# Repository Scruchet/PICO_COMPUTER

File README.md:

# PICO Computer Project: Motherboard

Welcome to my PICO Computer project repository. This section consolidates all the source files written in the C language used by my motherboard, as well as the electronic components created with KiCad. The primary goal of this project is to create a motherboard that can be connected to other boards (screen, keyboard, network) to build a Pico Computer.

## Part 1: Motherboard
You can find all the plans for my board in the **Motherboard_pico** directory.

### Features
This board is composed of multiple components. The main IC is the Atmega328p, which acts as the processor. The FTDI serves as the connection between the USB port and the Atmega328p (it does not include USB). The AT45DB641E is the storage component of the computer. As this component works with 3.3V signals, a buffer is needed to convert the 5V signals from the Atmega328p to 3.3V. To connect all the other cards, there are 5 HE10 connectors. All the different cards communicate using SPI (MOSI, MISO, SS, SCK).

## Part 2: Source Section (src)

This section includes all the source files written in the C language used by my motherboard. In addition to the source files, there is also a test folder to demonstrate various evaluations performed during the project's development.

### Module Details

#### Makefile
The Makefile enables project compilation and management. Refer to this file for details on compilation, linking, and other build tasks. In each directory, you can run the code (excluding files without main.c) and upload the code using the `make upload` command.

#### Memory
The Memory directory contains files related to memory management, including handling a specific flash memory (AT45DB641E).

#### Scheduler
The Scheduler module includes files necessary for implementing a scheduler. Refer to `makefile`, `scheduler.c`, and `scheduler.h` for more details.

#### SPI
The SPI module contains the files `spi.c` and `spi.h` for managing communication via the Serial Peripheral Interface (SPI) bus.

#### UART
The UART module includes the files `UART.c` and `UART.h`, dedicated to asynchronous serial communication (UART).

#### Tests
The Tests directory includes several subdirectories, each containing specific tests.

- `7seg`: Tests related to the 7-segment display (https://www.sparkfun.com/products/11441).
- `Mat_leds`: Tests for the LED matrix (https://www.sparkfun.com/products/retired/760).
- `Mem`: Tests for memory management.
- `UART_SPI`: Tests for UART and SPI modules.

# Contact
Thank you for visiting my project. If you have any comments or questions, please feel free to contact me via email at the following address: cruchetsimon@gmail.com

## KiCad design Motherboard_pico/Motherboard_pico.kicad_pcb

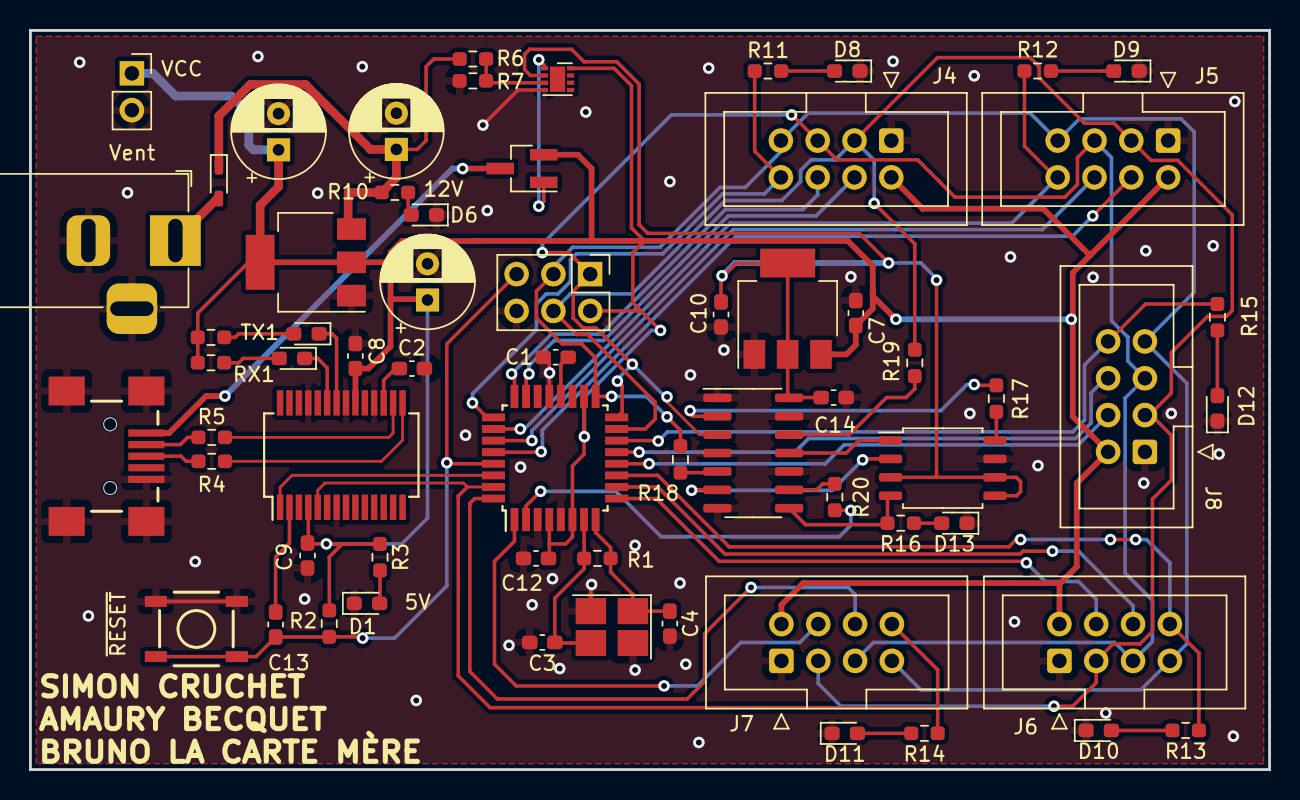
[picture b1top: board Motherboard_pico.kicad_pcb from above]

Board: 2 copper layers, 85.5 x 51.0 mm, 64 parts (0 on the bottom side), 58 nets.

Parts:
C1, C8, C9, C12, C13, C14: 100nF; C_0603_1608Metric_Pad1.08x0.95mm_HandSolder
C2: C; C_0603_1608Metric_Pad1.08x0.95mm_HandSolder
C3, C4: 22pF; C_0603_1608Metric_Pad1.08x0.95mm_HandSolder
C5: 4.7µF; CP_Radial_D6.3mm_P2.50mm
C6, C11: 47µF; CP_Radial_D6.3mm_P2.50mm
C7, C10: 1µF; C_0603_1608Metric_Pad1.08x0.95mm_HandSolder
D1, D6, D8, D9, D10, D11, D12, D13: LED; LED_0603_1608Metric_Pad1.05x0.95mm_HandSolder
D7: D; D_SC-80_HandSoldering
IC1: AT45DB641E-SHN2B-T; SOIC-8_5.275x5.275mm_P1.27mm
J1: Barrel_Jack_Switch_Pin3Ring; BarrelJack_Horizontal
J2: AVR-ISP-6; PinHeader_2x03_P2.54mm_Vertical
J3: Conn_01x02_Socket; PinSocket_1x02_P2.54mm_Vertical
J4, J5, J6, J7, J8: Conn_02x04_Counter_Clockwise; IDC-Header_2x04_P2.54mm_Vertical
J9: USB_MINI-B_SMT; USB-MINIB
Q1: FDN340P; SOT-23_Handsoldering
R1: 1MΩ; R_0603_1608Metric_Pad0.98x0.95mm_HandSolder
R2: 10KΩ; R_0603_1608Metric_Pad0.98x0.95mm_HandSolder
R3, R8, R9: 500Ω; R_0603_1608Metric_Pad0.98x0.95mm_HandSolder
R4, R5: 22Ω; R_0603_1608Metric_Pad0.98x0.95mm_HandSolder
R6, R7: 10k; R_0603_1608Metric_Pad0.98x0.95mm_HandSolder
R10: 1kΩ; R_0603_1608Metric_Pad0.98x0.95mm_HandSolder
R11, R12, R13, R14, R15, R16: 1k; R_0603_1608Metric_Pad0.98x0.95mm_HandSolder
R17, R18, R19, R20: 3.3k; R_0603_1608Metric_Pad0.98x0.95mm_HandSolder
RX1: LED; LED_0603_1608Metric_Pad1.05x0.95mm_HandSolder
S1: MOMENTARY-SWITCH-SPST-2-SMD-5.2MM; TACTILE_SWITCH_SMD_5.2MM
TX1: LED; LED_0603_1608Metric_Pad1.05x0.95mm_HandSolder
U1: ATmega328P-A; TQFP-32_7x7mm_P0.8mm
U2: LM358; DFN-8-1EP_2x2mm_P0.5mm_EP1.05x1.75mm
U3: AMS1117-5.0; SOT-223-3_TabPin2
U4: AMS1117; SOT-223-3_TabPin2
U5: 74LVC125; SOIC-14_3.9x8.7mm_P1.27mm
U6: FT232RL; SSOP-28_5.3x10.2mm_P0.65mm
Y1: 16MHz; Crystal_SMD_SeikoEpson_FA238-4Pin_3.2x2.5mm_HandSoldering

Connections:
3.3V: C10.1, C14.1, IC1.3 (~RESET), IC1.5 (~WP), IC1.6 (VCC), U2.2 (-), U4.2 (VO), U5.14 (VCC)
12V: C11.1, D7.1 (K), R6.2, R10.1, U3.3 (VI)
CBUS0: RX1.1 (K), U6.23 (CBUS0)
CBUS1: TX1.1 (K), U6.22 (CBUS1)
CS1: R20.1, U1.2 (PD4)
CS1_1: IC1.4 (~CS), R16.2, U5.8
CS2: J4.8, R11.2, U1.25 (PC2)
CS3: J5.8, R12.2, U1.26 (PC3)
CS4: J6.8, R13.2, U1.11 (PD7)
CS5: J7.8, R14.2, U1.31 (PD1), U6.5 (RXD)
CS6: J8.8, R15.2, U1.14 (PB2)
D+: R4.2, U6.15 (USBD+)
D-: R5.2, U6.16 (USBD-)
GND: C1.2, C2.2, C3.2, C4.2, C5.2, C6.2, C7.2, C8.2, C9.2, C10.2, C11.2, C12.2, C14.2, D1.1 (K), D6.1 (K), D8.1 (K), D9.1 (K), D10.1 (K), D11.1 (K), D12.1 (K), D13.1 (K), IC1.7 (GND), J1.2, J1.3, J2.6 (GND), J3.2, J4.1, J5.1, J6.1, J7.1, J8.1, J9.GND, J9.S1 (SHIELD), J9.S2 (SHIELD), J9.S3 (SHIELD), J9.S4 (SHIELD), R7.2, S1.1, S1.2, U1.3 (GND), U1.5 (GND), U1.21 (GND), U2.4 (V-), U3.1 (GND), U4.1 (ADJ), U5.1, U5.4, U5.7 (GND), U5.10, U5.13, U6.7 (GND), U6.18 (GND), U6.21 (GND), U6.25 (AGND), Y1.2, Y1.4
INT1: J4.4, U1.23 (PC0)
INT2: J5.4, U1.28 (PC5)
INT3: J6.4, U1.9 (PD5)
INT4: J7.4, U1.1 (PD3)
INT5: J8.4, U1.12 (PB0)
MISO: J2.1 (MISO), J4.5, J5.5, J6.5, J7.5, J8.5, U1.16 (PB4), U5.3
MISO_1: IC1.8 (SO), R17.1
MOSI: J2.4 (MOSI), J4.3, J5.3, J6.3, J7.3, J8.3, R19.1, U1.15 (PB3)
MOSI_1: IC1.1 (SI), U5.11
unnamed: D1.2 (A), R3.2
unnamed: D6.2 (A), R10.2
unnamed: D7.2 (A), J1.1
unnamed: D8.2 (A), R11.1
unnamed: D9.2 (A), R12.1
unnamed: D10.2 (A), R13.1
unnamed: D11.2 (A), R14.1
unnamed: D12.2 (A), R15.1
unnamed: D13.2 (A), R16.1
unnamed: J9.D+, R4.1
unnamed: J9.D-, R5.1
unnamed: Q1.1 (G), U2.1
unnamed: R17.2, U5.2
unnamed: R18.2, U5.5
unnamed: R19.2, U5.12
unnamed: R20.2, U5.9
unnamed: R8.2, RX1.2 (A)
unnamed: R9.2, TX1.2 (A)
unnamed: C1.1, U1.20 (AREF)
unnamed: C3.1, R1.2, U1.7 (XTAL1/PB6), Y1.3
unnamed: C4.1, R1.1, U1.8 (XTAL2/PB7), Y1.1
unnamed: R6.1, R7.1, U2.3 (+)
unnamed: C2.1, U6.17 (3V3OUT)
unnamed: C13.2, U6.2 (DTR)
RESET: C13.1, J2.5 (~RST), R2.2, S1.3, S1.4, U1.29 (~RESET/PC6)
RST1: J4.6, U1.24 (PC1)
RST2: J5.6, U1.27 (PC4)
RST3: J6.6, U1.10 (PD6)
RST4: J7.6, U1.32 (PD2)
RST5: J8.6, U1.13 (PB1)
SCK: J2.3 (SCK), J4.7, J5.7, J6.7, J7.7, J8.7, R18.1, U1.17 (PB5)
SCK_1: IC1.2 (SCK), U5.6
TX: U1.30 (PD0), U6.1 (TXD)
VCC: C5.1, C6.1, C7.1, C8.1, C9.1, C12.1, J2.2 (VCC), J3.1, J4.2, J5.2, J6.2, J7.2, J8.2, Q1.2 (S), R2.1, R3.1, R8.1, R9.1, U1.4 (VCC), U1.6 (VCC), U1.18 (AVCC), U2.8 (V+), U3.2 (VO), U4.3 (VI), U6.4 (VCCIO), U6.20 (VCC)
VUSB: J9.VBUS, Q1.3 (D)

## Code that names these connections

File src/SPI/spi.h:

#include <avr/interrupt.h>
#include <avr/io.h>
#include <avr/pgmspace.h>
#include <avr/sleep.h>
#include <stdio.h>
#include <util/delay.h>

#ifndef SPI_H
#define SPI_H

// Différents ports et leurs attributions
#define MOSI PB3
#define SCK PB5
#define MISO PB4
#define CS1 PD4
#define CS2 PC2
#define CS3 PC3
#define CS4 PD7
#define CS5 PD1
#define CS6 PB2

// Différentes commandes pour la transmission SPI
#define C_NET 0X76
#define C_LUM 0x7A
#define C_MIL 0x7B
#define C_CEN 0x7C
#define C_DIX 0x7D
#define C_UNI 0x7E
#define LUM_MAX 255

// Différentes couleur pour la matrice

#define MAT_BLACK 0x00
#define MAT_ROUGE 0xE0
#define MAT_VERT 0x1C
#define MAT_BLEU 0x03
#define MAT_VIOLET 0xE3
#define MAT_LOBSTER 0x1F
#define BLANC 0xFF

// Structure pour les différents esclaves
typedef struct cs {
    uint8_t pin;
    volatile uint8_t* port;
} cs_t;





// Prototype des fonctions
void spi_init();
void set_desactiver(cs_t tab_cs);
void set_activer(cs_t tab_cs);
uint8_t SPI_trans(uint8_t data);
void nettoyerEcran(cs_t tab_cs);
void luminosite_ecran(uint8_t value, cs_t cs);
void afficher_nombre(unsigned short int valeur, cs_t cs);
void mettre_couleur(uint8_t couleur, cs_t cs);
//
#endif // SPI_H

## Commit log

2023-12-29 project files
2023-12-29 Modification on README
2023-12-29 Sparkfun removed
2025-02-04 UART TEST
